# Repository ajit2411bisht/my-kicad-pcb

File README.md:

# ESP32-C3 PCB Design

## Overview

This project contains a custom PCB design based on the ESP32-C3.

The PCB was designed using KiCad and includes the main ESP32-C3 circuit along with sensor and user-interface sections.

## Tools Used

- KiCad

## Project Files

- `esp32demoproject.kicad_pro` - KiCad project file
- `esp32demoproject.kicad_pcb` - PCB layout
- `esp32-c3-02.kicad_sch` - ESP32-C3 schematic
- `sensors.kicad_sch` - Sensor section schematic
- `user_interface.kicad_sch` - User interface schematic

## Features

- ESP32-C3 based design
- Sensor interface
- User interface section
- Custom PCB layout
- Hierarchical schematic design

## PCB Design

The PCB layout was designed and reviewed using KiCad.

## Author

Ajit Bisht

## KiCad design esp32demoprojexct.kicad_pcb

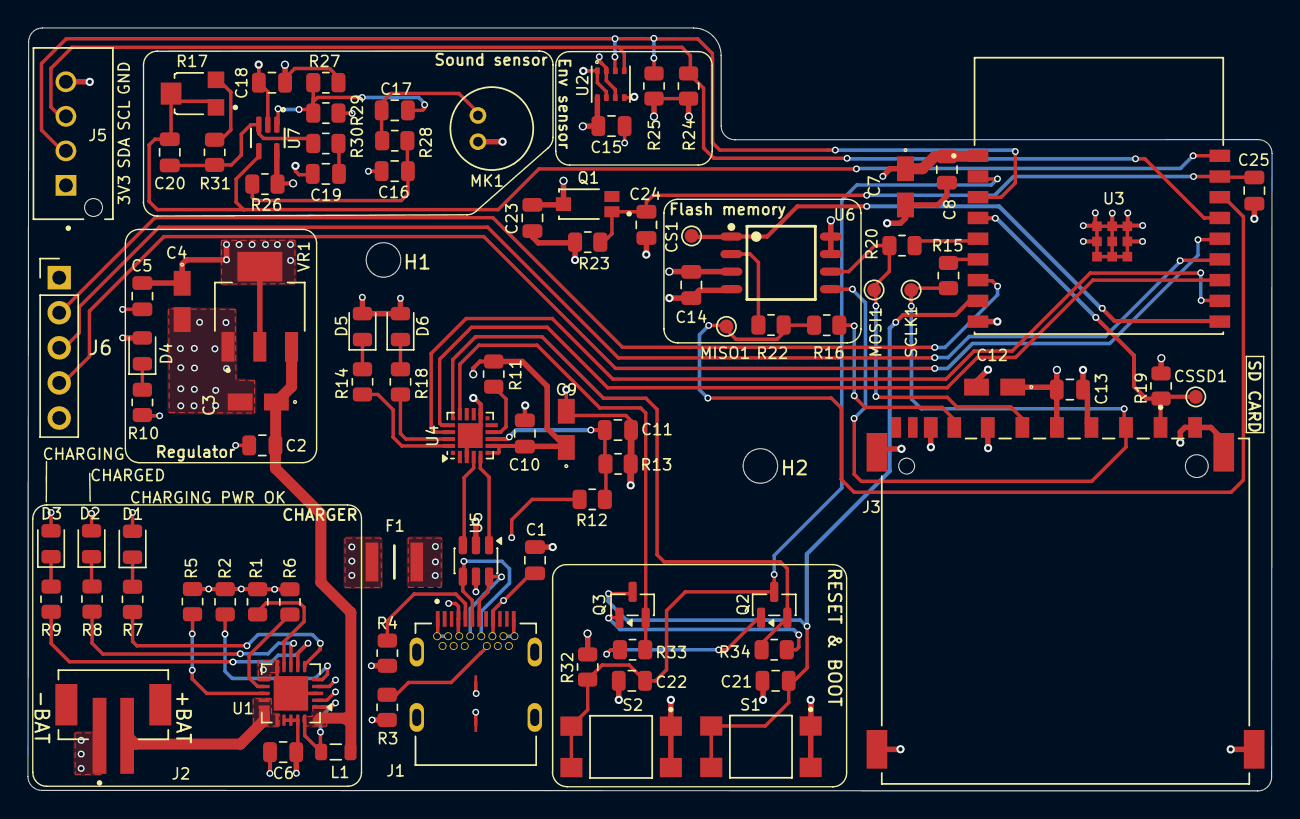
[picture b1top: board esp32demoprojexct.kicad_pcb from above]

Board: 4 copper layers, 90.0 x 55.2 mm, 92 parts (0 on the bottom side), 60 nets.

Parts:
C1, C2, C5, C8, C10, C13, C14, C15, C16, C18, C19, C20, C21, C22, C23: 0.1u; C_0805_2012Metric
C3, C4, C7, C12: 10u; T491A
C6, C11: 1u; C_0805_2012Metric
C9: 4.7u; T491A
C17, C24, C25: 10n; C_0805_2012Metric
CS1: Test CS; TestPoint_Pad_D1.0mm
CSSD1: Test CS_SD; TestPoint_Pad_D1.0mm
D1: Red; LED_0805_2012Metric
D2: Green; LED_0805_2012Metric
D3: Blue; LED_0805_2012Metric
D4: red; LED_0805_2012Metric
D5: GREEN; LED_0805_2012Metric
D6: BLUE; LED_0805_2012Metric
F1: 0ZCH0110AF2E; FUSC3226X100N
H1, H2: MountingHole; MountingHole_2.5mm
J1: SS-52400-002; BELFUSE_SS-52400-002
J2: B2B-PH-SM4-TB; JST_B2B-PH-SM4-TB
J3: GSD090012SEU; AMPHENOL_GSD090012SEU
J5: B4B-XH-AM__LF__SN_; JST_B4B-XH-AM__LF__SN_
J6: Conn_01x05_Pin; PinHeader_1x05_P2.54mm_Vertical
L1: L_Ferrite; L_0805_2012Metric
MISO1: Test MISO; TestPoint_Pad_D1.0mm
MK1: CMC-5042PF-AC; CUI_CMC-5042PF-AC
MOSI1: Test MOSI; TestPoint_Pad_D1.0mm
Q1: TEMT6000X01; TRANS_TEMT6000X01
Q2, Q3: BC817; SOT-23
R1, R2, R19, R23, R30, R32, R33, R34: 10k; R_0805_2012Metric
R3: 5.1k; R_0805_2012Metric
R4: 5k1; R_0805_2012Metric
R5, R26, R28: 2k; R_0805_2012Metric
R6: 20k; R_0805_2012Metric
R7, R8, R9, R14, R18: 470; R_0805_2012Metric
R10: 330; R_0805_2012Metric
R11: 1k; R_0805_2012Metric
R12: 22K1; R_0805_2012Metric
R13: 47K5; R_0805_2012Metric
R15, R16, R20, R22: 50R; R_0805_2012Metric
R17: 35WR100KLFTR; TRIM_35WR100KLFTR
R24, R25: 4k7; R_0805_2012Metric
R27, R29: 1M; R_0805_2012Metric
R31: 22k; R_0805_2012Metric
S1: BOOT BUTTON; SW_TL3305AF260QG
S2: RESET; SW_TL3305AF260QG
SCLK1: Test SCLK; TestPoint_Pad_D1.0mm
U1: MCP73871; QFN-20-1EP_4x4mm_P0.5mm_EP2.5x2.5mm
U2: BME280; PSON65P250X250X100-8N
U3: ESP32-C3-WROOM-02-H4; MODULE_ESP32-C3-WROOM-02-H4
U4: CP2102N-Axx-xQFN20; SiliconLabs_QFN-20-1EP_3x3mm_P0.5mm_EP1.8x1.8mm
U5: USBLC6-2SC6; SOT-23-6
U6: W25Q32JVSSIQ; SOIC127P790X216-8N
U7: MAX4466EXK; SOT65P210X110-5N
VR1: LM1117MPX-3.3; VREG_LM1117MPX-3.3_NOPB

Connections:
+3.3V: C4.1, C5.1, C7.1, C8.1, C9.1, C10.2, C12.1, C13.1, C14.1, C15.1, C18.1, C23.1, D4.2 (A), D5.2 (A), D6.2 (A), J3.4 (VDD1), J5.1, J6.1, Q1.3, R11.1, R19.1, R24.1, R25.1, R26.2, R27.2, R32.2, U2.2 (CSB), U2.6 (VDDIO), U2.8 (VDD), U3.1 (3V3), U4.6 (VDD), U4.7 (VREGIN), U6.3 (~WP(IO2)), U6.7 (~HOLD/~RESET(IO3)), U6.8 (VCC), U7.5 (VCC), VR1.2 (VOUT_2), VR1.4 (VOUT_4)
+5V: C2.1, C3.1, L1.2, VR1.3 (VIN)
/+5V_USB: C6.1, D1.2 (A), D2.2 (A), D3.2 (A), F1.2, U1.2 (VPCC), U1.4 (PROG2), U1.17 (CE), U1.18 (IN), U1.19 (IN)
/CHARGED: R8.2, U1.8 (STAT1/~LBO)
/CHARGING: R9.2, U1.7 (STAT2)
/CHARGING_POWER_GOOD: R7.2, U1.6 (~PG)
/ESP32-C3-02/BOOT: C21.1, Q3.3 (C), S1.2, S1.4, U3.8 (IO9)
/ESP32-C3-02/CS: CS1.1 (1_1), U3.10 (IO10), U6.1 (~CS)
/ESP32-C3-02/CS_SD: CSSD1.1 (1_1), J3.1 (CD/DAT3), R19.2, U3.4 (IO5)
/ESP32-C3-02/DTS: Q3.2 (E), R33.1, U4.15 (~CTS)
/ESP32-C3-02/EN: C22.1, Q2.3 (C), R32.1, S2.2, S2.4, U3.2 (EN)
/ESP32-C3-02/GPIO8: J6.2, U3.7 (IO8)
/ESP32-C3-02/GPIO18: J6.3, U3.13 (IO18)
/ESP32-C3-02/GPIO19: J6.4, U3.14 (IO19)
/ESP32-C3-02/MIC_OUT: C20.2, R17.1, R17.2, U3.18 (IO0), U7.4 (OUT)
/ESP32-C3-02/MISO_DO: MISO1.1 (1_1), R16.1, R22.2, U3.16 (IO2)
/ESP32-C3-02/MOSI_DI: J3.2 (CMD), MOSI1.1 (1_1), R15.1, U6.5 (DI(IO0))
/ESP32-C3-02/PHOTO_S: C24.1, C25.1, Q1.1, R23.1, U3.17 (IO1)
/ESP32-C3-02/RTS: Q2.2 (E), R34.1, U4.16 (~RTS)
/ESP32-C3-02/RX_TX: U3.12 (TXD), U4.17 (RXD)
/ESP32-C3-02/SCL: J5.3, R24.2, U2.4 (SCK), U3.15 (IO3)
/ESP32-C3-02/SCLK: J3.5 (CLK), R20.2, SCLK1.1 (1_1), U6.6 (CLK)
/ESP32-C3-02/SDA: J5.2, R25.2, U2.3 (SDI), U3.3 (IO4)
/ESP32-C3-02/TX_RX: U3.11 (RXD), U4.18 (TXD)
/ESP32-C3-02/USB_D+: U4.4 (D+), U5.3 (I/O2)
/ESP32-C3-02/USB_D-: U4.5 (D-), U5.1 (I/O1)
/USB_DN: J1.A7 (DN1), J1.B7 (DN2), U5.6 (I/O1)
/USB_DP: J1.A6 (DP1), J1.B6 (DP2), U5.4 (I/O2)
/VBAT: J2.2, U1.14 (V_{BAT}), U1.15 (V_{BAT}), U1.16 (V_{BAT_SENSE})
/VBUS: C1.1, F1.1, J1.A4 (VBUSA1), J1.A9 (VBUSA2), J1.B4 (VBUSB1), J1.B9 (VBUSB2), R12.1, U5.5 (VBUS)
/pwr_led: D4.1 (K), R10.2
GND: C1.2, C2.2, C3.2, C4.2, C5.2, C6.2, C7.2, C8.2, C9.2, C10.1, C11.2, C12.2, C13.2, C14.2, C15.2, C16.1, C18.2, C19.1, C21.2, C22.2, C23.2, C24.2, C25.2, J1.A1 (GNDA1), J1.A12 (GNDA2), J1.B1 (GNDB1), J1.B12 (GNDB2), J1.G1 (GND/SHIELD), J1.G2 (GND/SHIELD), J1.G3 (GND/SHIELD), J1.G4 (GND/SHIELD), J1.S1 (GND/SHIELD), J1.S2 (GND/SHIELD), J1.S3 (GND/SHIELD), J1.S4 (GND/SHIELD), J2.1, J3.3 (VSS1), J3.6 (VSS2), J3.8 (DAT1), J3.9 (DAT2), J3.G1 (SHIELD_GND), J3.G2 (SHIELD_GND), J3.G3 (SHIELD_GND), J3.G4 (SHIELD_GND), J5.4, J6.5, MK1.GND, R1.2, R2.2, R3.1, R4.1, R5.1, R6.1, R10.1, R13.2, R23.2, R29.1, S1.1, S1.3, S2.1, S2.3, U1.3 (SEL), U1.10 (V_{SS}), U1.11 (V_{SS}), U1.21 (V_{SS}), U2.1 (GND), U2.5 (SDO), U2.7 (GND), U3.9 (GND), U3.19 (GND), U3.20 (GND), U3.21 (GND), U3.22 (GND), U3.23 (GND), U3.24 (GND), U3.25 (GND), U3.26 (GND), U3.27 (GND), U4.3 (GND), U4.12 (GND), U4.21 (GND), U5.2 (GND), U6.4 (GND), U7.2 (GND), VR1.1 (GND)
unnamed: C16.2, R26.1, R28.2
unnamed: C17.1, MK1.OUT, R28.1
unnamed: C19.2, R30.1
unnamed: D1.1 (K), R7.1
unnamed: D2.1 (K), R8.1
unnamed: D3.1 (K), R9.1
unnamed: D5.1 (K), R14.1
unnamed: D6.1 (K), R18.1
unnamed: J1.A5 (CC1), R4.2
unnamed: J1.B5 (CC2), R3.2
unnamed: J3.7 (DAT0), R16.2
unnamed: L1.1, U1.1 (OUT), U1.20 (OUT)
unnamed: Q2.1 (B), R33.2
unnamed: Q3.1 (B), R34.2
unnamed: R17.3, R31.2
unnamed: R5.2, U1.13 (PROG1)
unnamed: R6.2, U1.12 (PROG3)
unnamed: R2.1, U1.5 (THERM)
unnamed: R1.1, U1.9 (~TE)
unnamed: R20.1, U3.5 (IO6)
unnamed: R15.2, U3.6 (IO7)
unnamed: C11.1, R12.2, R13.1, U4.8 (VBUS)
unnamed: R11.2, U4.9 (~RST)
unnamed: R18.2, U4.19 (~RXT/GPIO.3)
unnamed: R14.2, U4.20 (~TXT/GPIO.2)
unnamed: R22.1, U6.2 (DO(IO1))
unnamed: C17.2, R27.1, R29.2, U7.1 (IN+)
unnamed: C20.1, R30.2, R31.1, U7.3 (IN-)
